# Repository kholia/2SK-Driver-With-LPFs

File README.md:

This PCB was validated in July, 2023.

It outputs around 210mW into a dummy load @ 28 MHz even without any matching at
the output side. This is more than enough to drive RD16HHF1-501 easily.

Input is ~10mW straight from a Si5351 clone module.

We should probably add some simple LC matching at the output side one day.

Measurements on tinySA after 50 dB attentuation:

```
-24.4 dBm - Fc

-71.9 dBm -> second harmonic

dBc = ~47
```

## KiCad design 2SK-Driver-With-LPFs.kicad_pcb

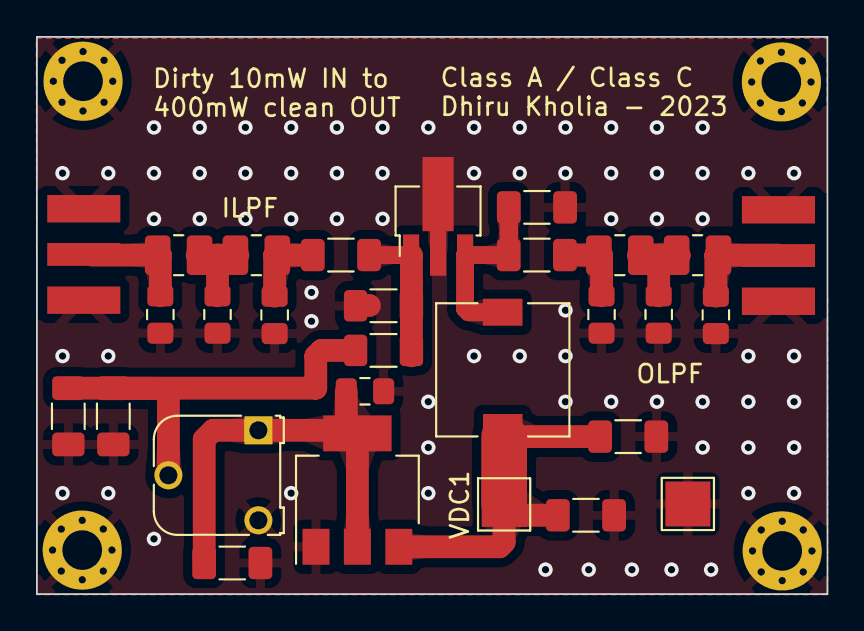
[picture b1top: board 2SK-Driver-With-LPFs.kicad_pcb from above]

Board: 2 copper layers, 43.9 x 31.0 mm, 33 parts (0 on the bottom side), 12 nets.

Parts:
C1, C3, C7, C9: 120p; C_0805_2012Metric_Pad1.18x1.45mm_HandSolder
C2, C8: 200p; C_0805_2012Metric_Pad1.18x1.45mm_HandSolder
C4: 10n; C_1206_3216Metric_Pad1.33x1.80mm_HandSolder
C5: 100pF; C_1206_3216Metric_Pad1.33x1.80mm_HandSolder
C6, C12, C15: 100nF; C_1206_3216Metric_Pad1.33x1.80mm_HandSolder
C10: 10uF/16V; C_1206_3216Metric_Pad1.33x1.80mm_HandSolder
C11: 100nF; C_0805_2012Metric_Pad1.18x1.45mm_HandSolder
C13: 10uF/50V; C_1206_3216Metric_Pad1.33x1.80mm_HandSolder
C14: 10nF; C_1206_3216Metric_Pad1.33x1.80mm_HandSolder
GND1: Conn_01x01; TestPoint_Pad_2.5x2.5mm
H1, H2, H3, H4: MountingHole_Pad; MountingHole_2.2mm_M2_Pad_Via
L1, L2, L4, L5: 360n; L_1008_2520Metric_Pad1.43x2.20mm_HandSolder
L3: 3.3uH; L_7.3x7.3_H3.5
Q1: 2SK3475; SOT-89-3_Handsoldering
R1: 1M; R_1206_3216Metric_Pad1.30x1.75mm_HandSolder
R2: 10k; R_1206_3216Metric_Pad1.30x1.75mm_HandSolder
RV1: 10k; Potentiometer_Runtron_RM-065_Vertical
SMA1, SMA2: SMA; SMA_EDGELAUNCH_Modded
U1: NCP1117ST50T3G; SOT-223-3_TabPin2
VDC1: Conn_01x01; TestPoint_Pad_2.5x2.5mm

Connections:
+5V: C10.1, C11.1, RV1.1, U1.2 (VO)
+12V: C12.1, C13.1, L3.1, U1.3 (VI), VDC1.1
BIAS: C4.2, Q1.1 (G), R1.1, R2.2
GND: C1.2, C2.2, C3.2, C5.2, C7.2, C8.2, C9.2, C10.2, C11.2, C12.2, C13.2, C14.1, C15.1, GND1.1, H1.1, H2.1, H3.1, H4.1, Q1.2 (S), R1.2, RV1.3, SMA1.2 (Ext), SMA2.2 (Ext), U1.1 (GND)
unnamed: C2.1, L1.2, L2.1
unnamed: C3.1, C4.1, L2.2
unnamed: C6.1, C7.1, L4.1
unnamed: C8.1, L4.2, L5.1
unnamed: C14.2, C15.2, R2.1, RV1.2
unnamed: C5.1, C6.2, L3.2, Q1.3 (D)
unnamed: C1.1, L1.1, SMA1.1 (In)
unnamed: C9.1, L5.2, SMA2.1 (In)
